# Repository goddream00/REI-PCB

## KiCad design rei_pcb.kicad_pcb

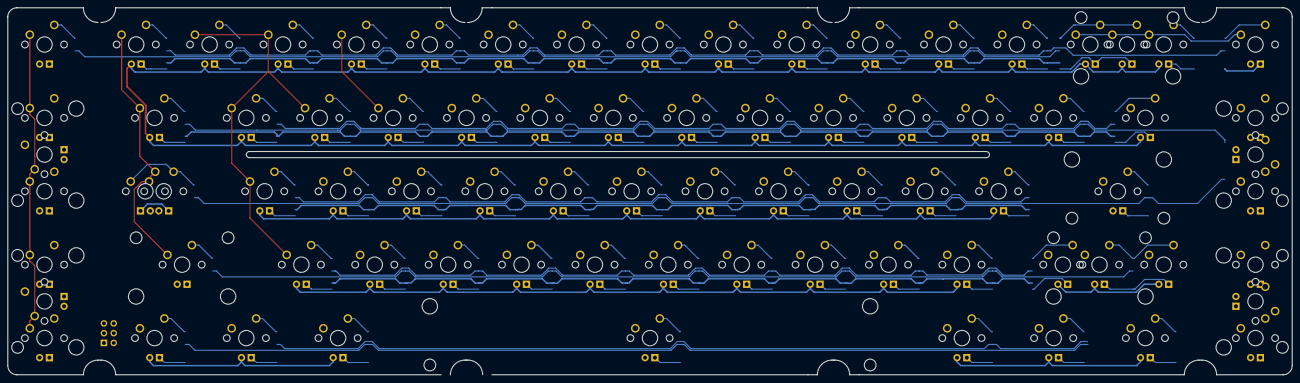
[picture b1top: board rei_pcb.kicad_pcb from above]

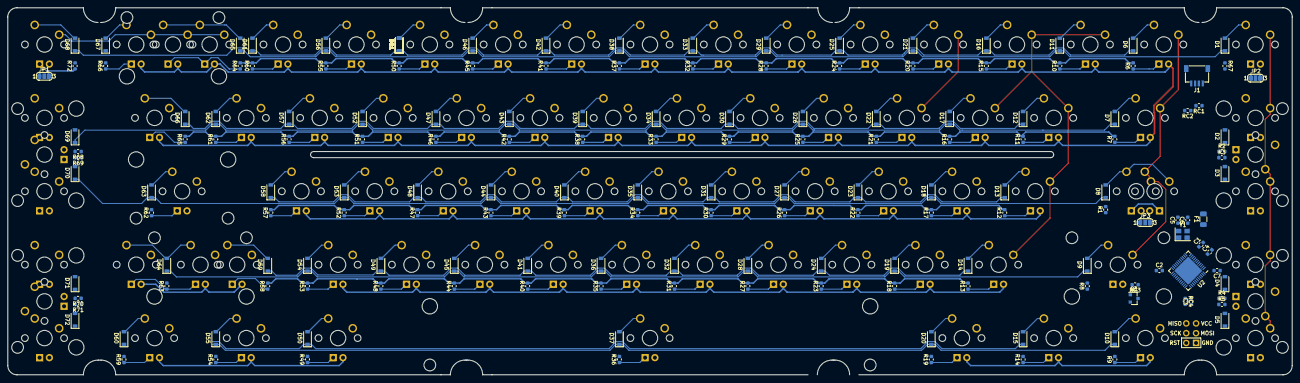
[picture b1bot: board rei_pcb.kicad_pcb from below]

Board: 2 copper layers, 333.4 x 95.3 mm, 248 parts (169 on the bottom side), 183 nets.

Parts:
C1, C2, C3: 0.1uF; C_0603_1608Metric
C4: 1uF; C_0603_1608Metric
C5, C6: 22pF; C_0603_1608Metric
C7: 10uF; C_0603_1608Metric
D1, D2, D3, D4, D5, D6, D7, D8, D9, D10, D11, D12, D13, D14, D15, D16, D17, D18, D19, D20, D21, D22, D23, D24, D25, D26, D27, D28, D29, D30, D31, D32, D33, D34, D35, D36, D37, D38, D39, D40, D41, D42, D43, D44, D45, D46, D47, D48, D49, D50, D51, D51#2, D51#3, D51#4, D51#5, D51#6, D52, D53, D54, D55, D56, D57, D58, D59, D60, D61, D62, D63, D64, D65, D66, D67, D68, D69, D70, D71, D72: D_Small; D_SOD-123
F1: 500mA; Fuse_1206_3216Metric
J1: SM04B-SRSS-TB(LF)(SN); JST-SR-4
J2: AVR-ISP-6; Reset_Pretty-Mask
JP1, JP2, JP3: SolderJumper_3_Open; SolderJumper-3_P1.3mm_Open_RoundedPad1.0x1.5mm_NumberLabels
MX_0, MX_1, MX_2, MX_3, MX_4, MX_5, MX_6, MX_7, MX_8, MX_9, MX_.1: MX-LED; MXOnly-1U
MX_'1: MX-LED; MXOnly-1U
MX_,1: MX-LED; MXOnly-1U
MX_-1: MX-LED; MXOnly-1U
MX_/1: MX-LED; MXOnly-1U
MX_;1: MX-LED; MXOnly-1U
MX_=1: MX-LED; MXOnly-1U
MX_A1: MX-LED; MXOnly-1U
MX_B1: MX-LED; MXOnly-1U
MX_BSPACE1: MX-LED; MXOnly-2U
MX_BSPACE2, MX_BSPACE3: MX-LED; MXOnly-1U
MX_C1: MX-LED; MXOnly-1U
MX_CLOCK1: MX-LED; MXOnly-1.75U
MX_CLOCKSTEP1: MX-LED; MXOnly-1.25U-FLIPPED
MX_D1: MX-LED; MXOnly-1U
MX_E1: MX-LED; MXOnly-1U
MX_ENTER1: MX-LED; MXOnly-2.25U-ReversedStabilizers
MX_ESC1: MX-LED; MXOnly-1U
MX_F1, MX_F2, MX_F3, MX_F4, MX_F5, MX_F6, MX_F7, MX_F8, MX_F9, MX_F10: MX-LED; MXOnly-1U
MX_F1V1, MX_F3V1, MX_F6V1, MX_F8V1: MX-LED; MXOnly-2U
MX_G1: MX-LED; MXOnly-1U
MX_H1: MX-LED; MXOnly-1U
MX_I1: MX-LED; MXOnly-1U
MX_J1: MX-LED; MXOnly-1U
MX_K1: MX-LED; MXOnly-1U
MX_L1: MX-LED; MXOnly-1U
MX_LALT1: MX-LED; MXOnly-1.5U
MX_LCTRL1: MX-LED; MXOnly-1.5U
MX_LGUI1: MX-LED; MXOnly-1U
MX_LSHIFT1: MX-LED; MXOnly-2.25U
MX_M1: MX-LED; MXOnly-1U
MX_N1: MX-LED; MXOnly-1U
MX_O1: MX-LED; MXOnly-1U
MX_P1: MX-LED; MXOnly-1U
MX_Q1: MX-LED; MXOnly-1U
MX_R1: MX-LED; MXOnly-1U
MX_RALT1: MX-LED; MXOnly-1.5U
MX_RCTRL1: MX-LED; MXOnly-1.5U
MX_RGUI1: MX-LED; MXOnly-1U
MX_RSHIFT1: MX-LED; MXOnly-2.75U
MX_RSHIFTSPLIT1: MX-LED; MXOnly-1.75U
MX_S1: MX-LED; MXOnly-1U
MX_SPACE1: MX-LED; MXOnly-7U-ReversedStabilizers
MX_SPLITFN1: MX-LED; MXOnly-1U
MX_T1: MX-LED; MXOnly-1U
MX_TAB1: MX-LED; MXOnly-1.5U
MX_TILDE1: MX-LED; MXOnly-1U
MX_U1: MX-LED; MXOnly-1U
MX_V1: MX-LED; MXOnly-1U
MX_W1: MX-LED; MXOnly-1U
MX_X1: MX-LED; MXOnly-1U
MX_Y1: MX-LED; MXOnly-1U
MX_Z1: MX-LED; MXOnly-1U
MX_[1: MX-LED; MXOnly-1U
MX_\1: MX-LED; MXOnly-1.5U
MX_]1: MX-LED; MXOnly-1U
Q1: 2N7002; SOT-23
R1, R2, R3, R4, R5, R6, R7, R8, R9, R10, R11, R12, R13, R14, R15, R16, R17, R18, R19, R20, R21, R22, R23, R24, R25, R26, R27, R28, R29, R30, R31, R32, R33, R34, R35, R36, R37, R38, R39, R40, R41, R42, R43, R44, R45, R46, R47, R48, R49, R50, R51, R52, R53, R54, R55, R56, R57, R58, R59, R60, R61, R62, R63, R64, R65, R66, R67, R68, R69, R70, R71, R72: 1k; R_0603_1608Metric
RC1, RC2: 22; R_0603_1608Metric
RC3: 1.5k; R_0603_1608Metric
RC4: 10k; R_0603_1608Metric
U2: ATmega32U4RC-MU; QFN-44-1EP_7x7mm_P0.5mm_EP5.2x5.2mm
Y1: 16MHz; Crystal_SMD_3225-4Pin_3.2x2.5mm

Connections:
+5V: C1.1, C2.1, C3.1, C7.1, F1.1, J2.2, MX_0.3, MX_1.3, MX_2.3, MX_3.3, MX_4.3, MX_5.3, MX_6.3, MX_7.3, MX_8.3, MX_9.3, MX_'1.3, MX_,1.3, MX_-1.3, MX_.1.3, MX_/1.3, MX_;1.3, MX_=1.3, MX_A1.3, MX_B1.3, MX_BSPACE1.3, MX_BSPACE2.3, MX_BSPACE3.3, MX_C1.3, MX_CLOCK1.3, MX_CLOCKSTEP1.3, MX_D1.3, MX_E1.3, MX_ENTER1.3, MX_ESC1.3, MX_F1.3, MX_F1V1.3, MX_F2.3, MX_F3.3, MX_F3V1.3, MX_F4.3, MX_F5.3, MX_F6.3, MX_F6V1.3, MX_F7.3, MX_F8.3, MX_F8V1.3, MX_F9.3, MX_F10.3, MX_G1.3, MX_H1.3, MX_I1.3, MX_J1.3, MX_K1.3, MX_L1.3, MX_LALT1.3, MX_LCTRL1.3, MX_LGUI1.3, MX_LSHIFT1.3, MX_M1.3, MX_N1.3, MX_O1.3, MX_P1.3, MX_Q1.3, MX_R1.3, MX_RALT1.3, MX_RCTRL1.3, MX_RGUI1.3, MX_RSHIFT1.3, MX_RSHIFTSPLIT1.3, MX_S1.3, MX_SPACE1.3, MX_SPLITFN1.3, MX_T1.3, MX_TAB1.3, MX_TILDE1.3, MX_U1.3, MX_V1.3, MX_W1.3, MX_X1.3, MX_Y1.3, MX_Z1.3, MX_[1.3, MX_\1.3, MX_]1.3, U2.2, U2.7, U2.14, U2.24, U2.34, U2.44
CAPS_IND: JP3.3, U2.11
CAPS_LEDGND: J2.1, MX_CLOCK1.4, MX_CLOCKSTEP1.4, R1.1
COL0: MX_CLOCK1.1, MX_CLOCKSTEP1.2, MX_ESC1.1, MX_F1.1, MX_F1V1.1, MX_F2.1, MX_F3.1, MX_F3V1.1, MX_F4.1, MX_LCTRL1.1, MX_LSHIFT1.1, MX_TAB1.1, MX_TILDE1.1, U2.41
COL1: MX_1.1, MX_2.1, MX_A1.1, MX_LALT1.1, MX_LGUI1.1, MX_Q1.1, MX_S1.1, MX_W1.1, MX_X1.1, MX_Z1.1, U2.40
COL2: MX_3.1, MX_4.1, MX_C1.1, MX_D1.1, MX_E1.1, MX_F10.1, MX_R1.1, MX_V1.1, U2.39
COL3: MX_5.1, MX_6.1, MX_B1.1, MX_G1.1, MX_H1.1, MX_N1.1, MX_SPACE1.1, MX_T1.1, MX_Y1.1, U2.38
COL4: MX_7.1, MX_8.1, MX_,1.1, MX_I1.1, MX_J1.1, MX_K1.1, MX_M1.1, MX_U1.1, U2.37
COL5: MX_0.1, MX_9.1, MX_.1.1, MX_/1.1, MX_;1.1, MX_L1.1, MX_O1.1, MX_P1.1, MX_RALT1.1, MX_RGUI1.1, U2.36
COL6: MX_'1.1, MX_-1.1, MX_=1.1, MX_ENTER1.1, MX_RCTRL1.1, MX_RSHIFT1.1, MX_RSHIFTSPLIT1.1, MX_SPLITFN1.1, MX_[1.1, MX_]1.1, U2.32
COL7: MX_BSPACE1.1, MX_BSPACE2.1, MX_BSPACE3.1, MX_F5.1, MX_F6.1, MX_F6V1.1, MX_F7.1, MX_F8.1, MX_F8V1.1, MX_F9.1, MX_\1.1, U2.8
D+: J1.3, RC2.2
D-: J1.2, RC1.2
ESC_IND: JP2.3, U2.9
ESC_LEDGND: J2.3, MX_ESC1.4, R67.1
GND: C1.2, C2.2, C3.2, C4.2, C5.2, C6.2, C7.2, J1.4, J2.6, Q1.2, RC4.2, U2.5, U2.15, U2.23, U2.35, U2.43, U2.45, Y1.2, Y1.4
LEDGND: JP1.1, JP2.1, JP3.1, Q1.3, R2.2, R3.2, R4.2, R5.2, R6.2, R7.2, R8.2, R9.2, R10.2, R11.2, R12.2, R13.2, R14.2, R15.2, R16.2, R17.2, R18.2, R19.2, R20.2, R21.2, R22.2, R23.2, R24.2, R25.2, R26.2, R27.2, R28.2, R29.2, R30.2, R31.2, R32.2, R33.2, R34.2, R35.2, R36.2, R37.2, R38.2, R39.2, R40.2, R41.2, R42.2, R43.2, R44.2, R45.2, R46.2, R47.2, R48.2, R49.2, R50.2, R51.2, R52.2, R53.2, R54.2, R55.2, R56.2, R57.2, R58.2, R59.2, R60.2, R61.2, R62.2, R63.2, R64.2, R65.2, R66.2, R68.2, R69.2, R70.2, R71.2
unnamed: C4.1, U2.6
unnamed: C5.1, U2.17, Y1.1
unnamed: C6.1, U2.16, Y1.3
unnamed: D1.2, MX_ESC1.2
unnamed: D2.2, MX_F1.2, MX_F1V1.2
unnamed: D3.2, MX_F2.2
unnamed: D4.2, MX_F3.2, MX_F3V1.2
unnamed: D5.2, MX_F4.2
unnamed: D6.2, MX_TILDE1.2
unnamed: D7.2, MX_TAB1.2
unnamed: D8.2, MX_CLOCK1.2, MX_CLOCKSTEP1.1
unnamed: D9.2, MX_LSHIFT1.2
unnamed: D10.2, MX_LCTRL1.2
unnamed: D11.2, MX_1.2
unnamed: D12.2, MX_Q1.2
unnamed: D13.2, MX_A1.2
unnamed: D14.2, MX_Z1.2
unnamed: D15.2, MX_LGUI1.2
unnamed: D16.2, MX_2.2
unnamed: D17.2, MX_W1.2
unnamed: D18.2, MX_S1.2
unnamed: D19.2, MX_X1.2
unnamed: D20.2, MX_LALT1.2
unnamed: D21.2, MX_3.2
unnamed: D22.2, MX_E1.2
unnamed: D23.2, MX_D1.2
unnamed: D24.2, MX_C1.2
unnamed: D25.2, MX_4.2
unnamed: D26.2, MX_R1.2
unnamed: D27.2, MX_F10.2
unnamed: D28.2, MX_V1.2
unnamed: D29.2, MX_5.2
unnamed: D30.2, MX_T1.2
unnamed: D31.2, MX_G1.2
unnamed: D32.2, MX_B1.2
unnamed: D33.2, MX_6.2
unnamed: D34.2, MX_Y1.2
unnamed: D35.2, MX_H1.2
unnamed: D36.2, MX_N1.2
unnamed: D37.2, MX_SPACE1.2
unnamed: D38.2, MX_7.2
unnamed: D39.2, MX_U1.2
unnamed: D40.2, MX_J1.2
unnamed: D41.2, MX_M1.2
unnamed: D42.2, MX_8.2
unnamed: D43.2, MX_I1.2
unnamed: D44.2, MX_K1.2
unnamed: D45.2, MX_,1.2
unnamed: D46.2, MX_9.2
unnamed: D47.2, MX_O1.2
unnamed: D48.2, MX_L1.2
unnamed: D49.2, MX_.1.2
unnamed: D50.2, MX_RALT1.2
unnamed: D51.2, D51#2.2, D51#3.2, D51#4.2, D51#5.2, D51#6.2, MX_0.2
unnamed: D52.2, MX_P1.2
unnamed: D53.2, MX_;1.2
unnamed: D54.2, MX_/1.2
unnamed: D55.2, MX_RGUI1.2
unnamed: D56.2, MX_-1.2
unnamed: D57.2, MX_[1.2
unnamed: D58.2, MX_'1.2
unnamed: D59.2, MX_RSHIFTSPLIT1.2
unnamed: D60.2, MX_RCTRL1.2
unnamed: D61.2, MX_=1.2
unnamed: D62.2, MX_]1.2
unnamed: D63.2, MX_ENTER1.2
unnamed: D64.2, MX_RSHIFT1.2, MX_SPLITFN1.2
unnamed: D65.2, MX_BSPACE1.2, MX_BSPACE2.2
unnamed: D66.2, MX_\1.2
unnamed: D67.2, MX_BSPACE3.2
unnamed: D68.2, MX_F5.2
unnamed: D69.2, MX_F6.2, MX_F6V1.2
unnamed: D70.2, MX_F7.2
unnamed: D71.2, MX_F8.2, MX_F8V1.2
unnamed: D72.2, MX_F9.2
unnamed: JP1.2, R72.2
unnamed: JP2.2, R67.2
unnamed: JP3.2, R1.2
unnamed: MX_0.4, R50.1
unnamed: MX_1.4, R10.1
unnamed: MX_2.4, R15.1
unnamed: MX_3.4, R20.1
unnamed: MX_4.4, R24.1
unnamed: MX_5.4, R28.1
unnamed: MX_6.4, R32.1
unnamed: MX_7.4, R37.1
unnamed: MX_8.4, R41.1
unnamed: MX_9.4, R45.1
unnamed: MX_'1.4, R57.1
unnamed: MX_,1.4, R44.1
unnamed: MX_-1.4, R55.1
unnamed: MX_.1.4, R48.1
unnamed: MX_/1.4, R53.1
unnamed: MX_;1.4, R52.1
unnamed: MX_=1.4, R60.1
unnamed: MX_A1.4, R12.1
unnamed: MX_B1.4, R31.1
unnamed: MX_BSPACE1.4, MX_BSPACE2.4, R64.1
unnamed: MX_BSPACE3.4, R66.1
unnamed: MX_C1.4, R23.1
unnamed: MX_D1.4, R22.1
unnamed: MX_E1.4, R21.1
unnamed: MX_ENTER1.4, R62.1
unnamed: MX_F1.4, MX_F1V1.4, R2.1
unnamed: MX_F2.4, R3.1
unnamed: MX_F3.4, MX_F3V1.4, R4.1
unnamed: MX_F4.4, R5.1
unnamed: MX_F6.4, MX_F6V1.4, R68.1
unnamed: MX_F7.4, R69.1
unnamed: MX_F8.4, MX_F8V1.4, R70.1
unnamed: MX_F9.4, R71.1
unnamed: MX_F10.4, R26.1
unnamed: MX_G1.4, R30.1
unnamed: MX_H1.4, R34.1
unnamed: MX_I1.4, R42.1
unnamed: MX_J1.4, R39.1
unnamed: MX_K1.4, R43.1
unnamed: MX_L1.4, R47.1
unnamed: MX_LALT1.4, R19.1
unnamed: MX_LCTRL1.4, R9.1
unnamed: MX_LGUI1.4, R14.1
unnamed: MX_LSHIFT1.4, R8.1
unnamed: MX_M1.4, R40.1
unnamed: MX_N1.4, R35.1
unnamed: MX_O1.4, R46.1
unnamed: MX_P1.4, R51.1
unnamed: MX_Q1.4, R11.1
unnamed: MX_R1.4, R25.1
unnamed: MX_RALT1.4, R49.1
unnamed: MX_RCTRL1.4, R59.1
unnamed: MX_RGUI1.4, R54.1
unnamed: MX_RSHIFT1.4, MX_SPLITFN1.4, R63.1
unnamed: MX_RSHIFTSPLIT1.4, R58.1
unnamed: MX_S1.4, R17.1
unnamed: MX_SPACE1.4, R36.1
unnamed: MX_T1.4, R29.1
unnamed: MX_TAB1.4, R7.1
unnamed: MX_TILDE1.4, R6.1
unnamed: MX_U1.4, R38.1
unnamed: MX_V1.4, R27.1
unnamed: MX_W1.4, R16.1
unnamed: MX_X1.4, R18.1
unnamed: MX_Y1.4, R33.1
unnamed: MX_Z1.4, R13.1
unnamed: MX_[1.4, R56.1
unnamed: MX_\1.4, R65.1
unnamed: MX_]1.4, R61.1
unnamed: Q1.1, RC3.1
unnamed: RC1.1, U2.3
unnamed: RC2.1, U2.4
unnamed: RC3.2, U2.25
unnamed: RC4.1, U2.33
RESET: J2.5, U2.13
ROW0: D1.1, D11.1, D21.1, D29.1, D38.1, D46.1, D56.1, D65.1, U2.31
ROW1: D6.1, D16.1, D25.1, D33.1, D42.1, D51.1, D51#2.1, D51#3.1, D51#4.1, D51#5.1, D51#6.1, D61.1, D68.1, U2.30
ROW2: D2.1, D12.1, D22.1, D30.1, D39.1, D47.1, D57.1, D66.1, U2.29
ROW3: D7.1, D17.1, D26.1, D34.1, D43.1, D52.1, D62.1, D69.1, U2.28
ROW4: D3.1, D13.1, D23.1, D31.1, D40.1, D48.1, D58.1, D67.1, U2.26
ROW5: D8.1, D18.1, D27.1, D35.1, D44.1, D53.1, D63.1, D70.1, U2.27
ROW6: D4.1, D14.1, D24.1, D32.1, D41.1, D49.1, D59.1, U2.21
ROW7: D9.1, D19.1, D28.1, D36.1, D45.1, D54.1, D64.1, D71.1, U2.20
ROW8: D5.1, D15.1, D50.1, D60.1, U2.19
ROW9: D10.1, D20.1, D37.1, D55.1, D72.1, U2.18
TGR_IND: JP1.3, U2.10
TGR_LEDGND: J2.4, MX_F5.4, R72.1
VCC: F1.2, J1.1

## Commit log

2020-04-25 Start project
2020-04-25 Add submodules
2020-04-25 Add footprint libraries
2020-04-26 PCB escheme and layout
2020-04-26 Updating PCB
2020-04-27 update pcb
2020-04-29 PCB initial complete
2020-04-29 Gerber files
2020-06-18 Completed PCB
2021-01-19 Push update
